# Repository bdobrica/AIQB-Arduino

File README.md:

The content of this repository is provided "as is" with no implied warranty. Also the content is available under [Attribution-NonCommercial-NoDerivatives 4.0 International](https://creativecommons.org/licenses/by-nc-nd/4.0/legalcode).

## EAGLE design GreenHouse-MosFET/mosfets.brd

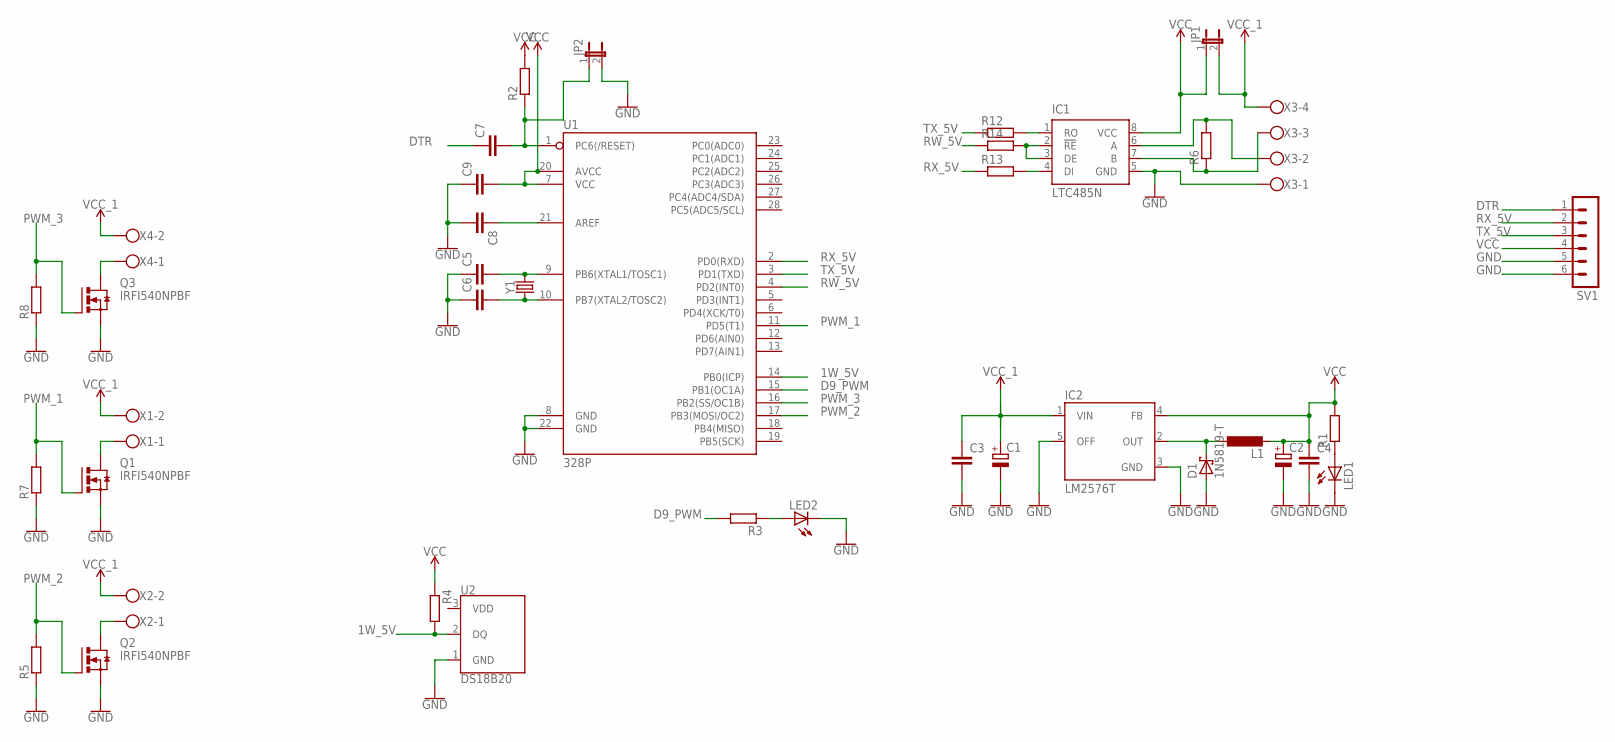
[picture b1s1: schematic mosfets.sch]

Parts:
C1, C2: CPOL-EUE5-10.5; E5-10,5
C3, C4, C5, C6, C7, C8, C9: C-EU025-025X050; C025-025X050
D1: 1N5819-T; DO41-7.6
IC1: LTC485N; DIL08
IC2: LM2576T; TO220-5
JP1, JP2: JP1E; JP1
L1: L-EUTJ3-U1; TJ3-U1
LED1, LED2: LED5MM
Q1, Q2, Q3: IRFI540NPBF; TO220BH
R1, R2, R3, R4, R5, R6, R7, R8, R12, R13, R14: R-EU_0204/7; 0204/7
SV1: MA06-1
U1: 328P; DIP28
U2: DS18B20; TO-92-AMMO
X1, X2, X4: W237-102
X3: W237-4
Y1: CRYSTALPTH-HC49US; HC49US

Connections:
1W_5V: R4.2, U1.14 (PB0(ICP)), U2.2 (DQ)
D9_PWM: R3.2, U1.15 (PB1(OC1A))
DTR: C7.1, SV1.1
GND: C1.-, C2.-, C3.2, C4.2, C5.1, C6.1, C8.2, C9.1, D1.A, IC1.5 (GND), IC2.3 (GND), IC2.5 (OFF), JP2.2, LED1.K (C), LED2.K (C), Q1.S, Q2.S, Q3.S, R5.1, R7.1, R8.1, SV1.5, SV1.6, U1.8 (GND), U1.22 (GND), U2.1 (GND), X3.1
unnamed: LED1.A, R1.1
unnamed: C5.2, U1.9 (PB6(XTAL1/TOSC1)), Y1.2
unnamed: C6.2, U1.10 (PB7(XTAL2/TOSC2)), Y1.1
unnamed: IC1.4 (DI), R13.2
unnamed: IC1.7 (B), R6.1, X3.3
unnamed: C8.1, U1.21 (AREF)
unnamed: LED2.A, R3.1
unnamed: IC1.1 (RO), R12.2
unnamed: D1.C, IC2.2 (OUT), L1.1
unnamed: C7.2, JP2.1, R2.1, U1.1 (PC6(/RESET))
unnamed: IC1.6 (A), R6.2, X3.2
unnamed: Q1.D, X1.1
unnamed: IC1.2 (!RE), IC1.3 (DE), R14.2
unnamed: Q2.D, X2.1
unnamed: Q3.D, X4.1
PWM_1: Q1.G, R7.2, U1.11 (PD5(T1))
PWM_2: Q2.G, R5.2, U1.17 (PB3(MOSI/OC2))
PWM_3: Q3.G, R8.2, U1.16 (PB2(SS/OC1B))
RW_5V: R14.1, U1.4 (PD2(INT0))
RX_5V: R13.1, SV1.2, U1.2 (PD0(RXD))
TX_5V: R12.1, SV1.3, U1.3 (PD1(TXD))
VCC: C2.+, C4.1, C9.2, IC1.8 (VCC), IC2.4 (FB), JP1.1, L1.2, R1.2, R2.2, R4.1, SV1.4, U1.7 (VCC), U1.20 (AVCC)
VCC_1: C1.+, C3.1, IC2.1 (VIN), JP1.2, X1.2, X2.2, X3.4, X4.2
VDD: U2.3 (VDD)

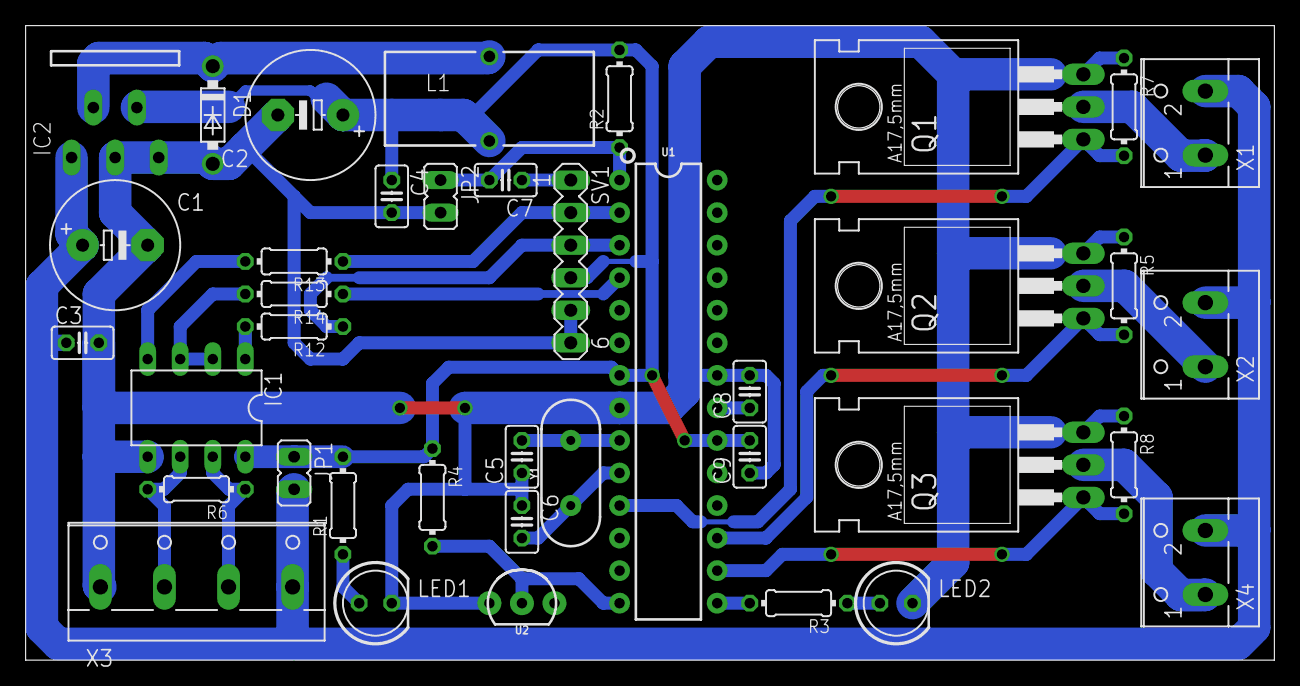
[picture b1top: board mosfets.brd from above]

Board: 2 copper layers, 97.5 x 49.5 mm, 39 parts (0 on the bottom side), 27 nets.

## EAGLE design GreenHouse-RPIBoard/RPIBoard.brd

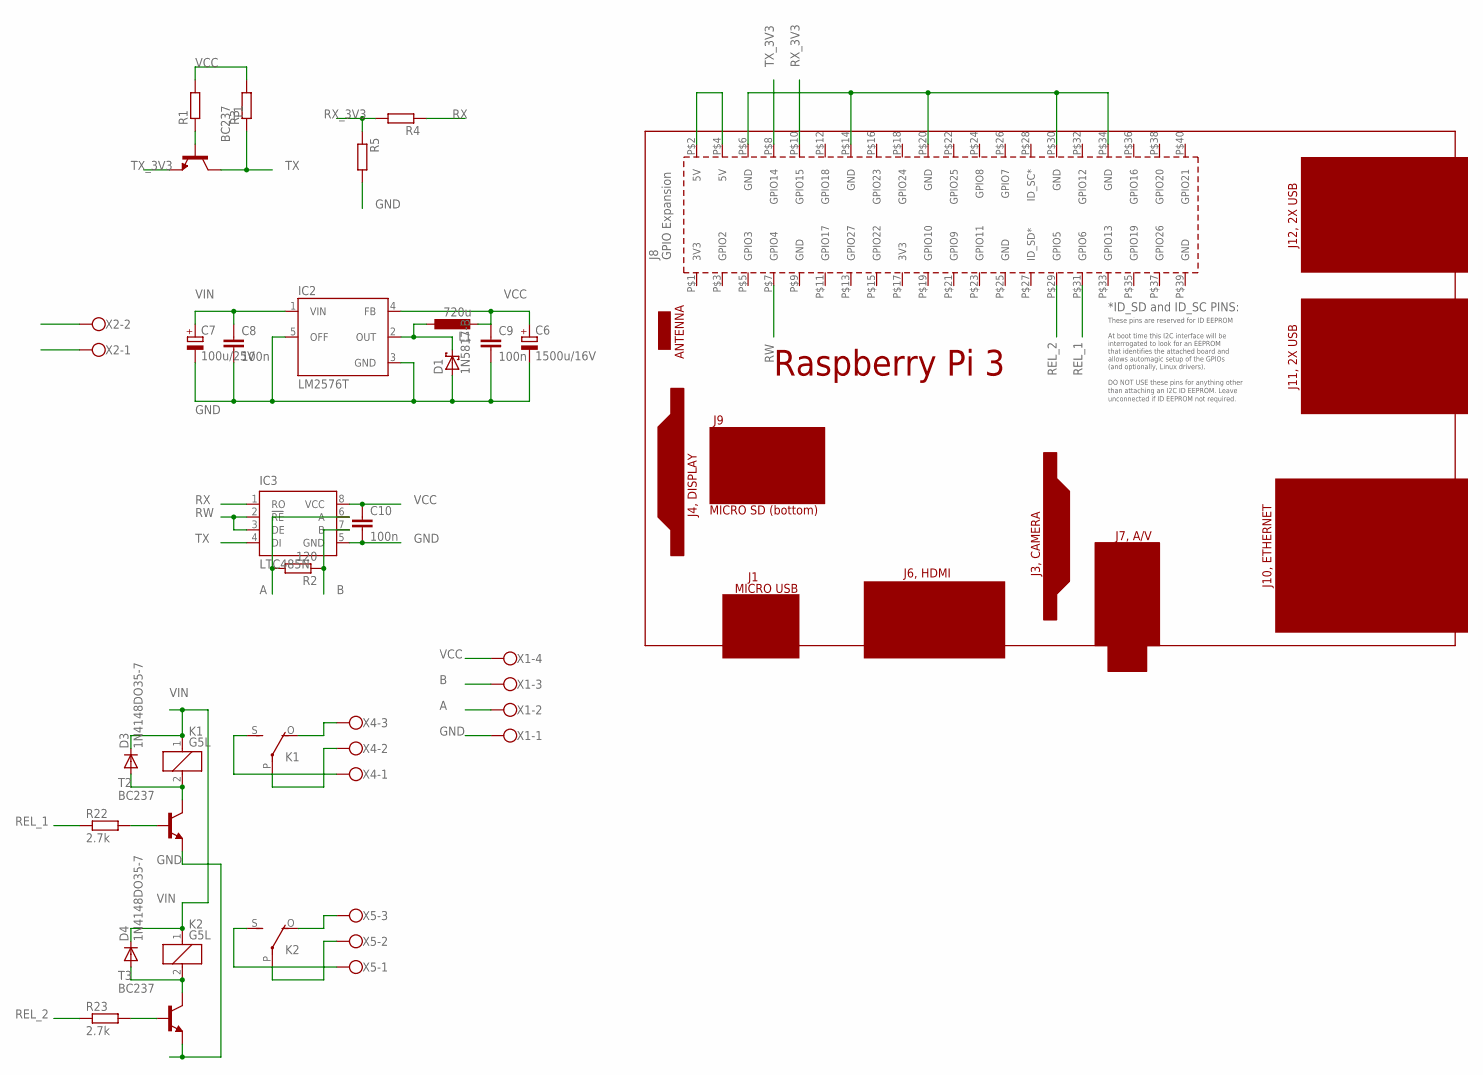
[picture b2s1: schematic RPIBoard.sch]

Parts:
C6: 1500u/16V; E5-10,5
C7: 100u/25V; E2,5-7
C8, C9, C10: 100n; C025-024X044
D1: 1N5817-B; DO41-7.6
D3, D4: 1N4148DO35-7; DO35-7
IC2: LM2576T; TO220-5
IC3: LTC485N; DIL08
K1, K2: G5L; G5LE
L1: 720u; TJ3-U1
PCB1: RPI3
R1, R3, R4, R5: R-EU_0207/7; 0207/7
R2: 120; 0204/7
R22, R23: 2.7k; 0204/7
T1, T2, T3: BC237; TO92
X1: W237-4
X2: W237-102
X4, X5: W237-103

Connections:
A: IC3.6 (A), R2.2, X1.2
B: IC3.7 (B), R2.1, X1.3
GND: C6.-, C7.-, C8.2, C9.2, C10.2, D1.A, IC2.3 (GND), IC2.5 (OFF), IC3.5 (GND), PCB1.P$6 (GND), PCB1.P$14 (GND), PCB1.P$20 (GND), PCB1.P$30 (GND), PCB1.P$34 (GND), R5.2, T2.1 (E), T3.1 (E), X1.1, X2.1
unnamed: R1.1, T1.2 (B)
unnamed: D1.C, IC2.2 (OUT), L1.1
unnamed: K2.O, X5.3
unnamed: K2.S, X5.1
unnamed: K1.S, X4.1
unnamed: K1.O, X4.3
unnamed: D3.A, K1.2, T2.3 (C)
unnamed: R22.2, T2.2 (B)
unnamed: K1.P, X4.2
unnamed: D4.A, K2.2, T3.3 (C)
unnamed: R23.2, T3.2 (B)
unnamed: K2.P, X5.2
REL_1: PCB1.P$31 (GPIO6), R22.1
REL_2: PCB1.P$29 (GPIO5), R23.1
RW: IC3.2 (!RE), IC3.3 (DE), PCB1.P$7 (GPIO4)
RX: IC3.1 (RO), R4.1
RX_3V3: PCB1.P$10 (GPIO15), R4.2, R5.1
TX: IC3.4 (DI), R3.1, T1.3 (C)
TX_3V3: PCB1.P$8 (GPIO14), T1.1 (E)
VCC: C6.+, C9.1, C10.1, IC2.4 (FB), IC3.8 (VCC), L1.2, PCB1.P$2 (5V), PCB1.P$4 (5V), R1.2, R3.2, X1.4
VIN: C7.+, C8.1, D3.C, D4.C, IC2.1 (VIN), K1.1, K2.1, X2.2

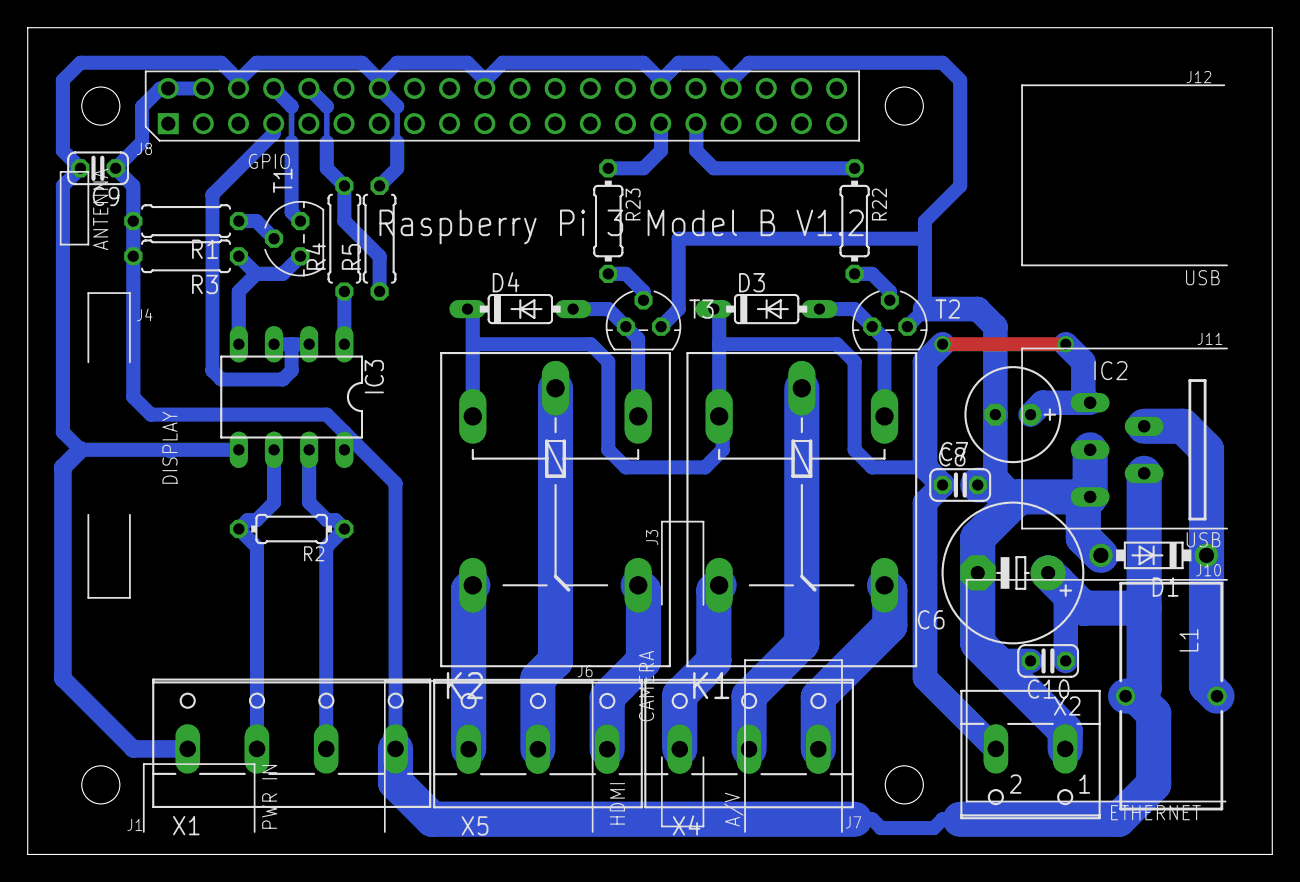
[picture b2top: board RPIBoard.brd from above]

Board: 2 copper layers, 89.8 x 59.7 mm, 28 parts (0 on the bottom side), 24 nets.

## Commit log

2017-07-09 :confetti_ball: Added .gitattributes & .gitignore files
2017-07-09 First Commit
    The boards and the Arduino library.
2017-07-10 Licensing
    The content of this repository is provided "as is" with no implied
    warranty. Also the content is available under
    [Attribution-NonCommercial-NoDerivatives 4.0
    International](https://creativecommons.org/licenses/by-nc-nd/4.0/legalcode).

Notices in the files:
parts and their libraries:
SparkFun-IC-Microcontroller: Licensing: Creative Commons ShareAlike 4.0 International - https://creativecommons.org/licenses/by-sa/4.0
